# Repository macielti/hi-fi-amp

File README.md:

# Hi-Fi Audio Amplifier project

Class A audio amplifier project based on JLH 1969 project.

Lista de componentes com valores aproximados: [Lista de Componentes Eletrônicos](https://github.com/macielti/hi-fi-amp/blob/main/docs/Lista%20de%20Componentes%20Eletrônicos.md)

## Exemplo da placa Fonte de Alimentação montada

## Exemplo da placa Amplificadora de Áudio montada

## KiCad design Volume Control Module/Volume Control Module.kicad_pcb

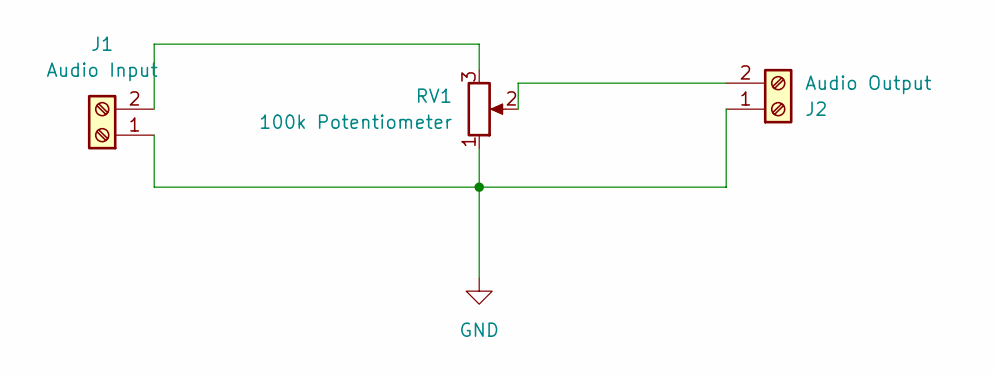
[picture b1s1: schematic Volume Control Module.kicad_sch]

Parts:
J1: Audio Input; TerminalBlock_MaiXu_MX126-5.0-02P_1x02_P5.00mm
J2: Audio Output; TerminalBlock_MaiXu_MX126-5.0-02P_1x02_P5.00mm
RV1: 100k Potentiometer; Potentiometer_Alps_RK163_Single_Horizontal

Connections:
GND: J1.1, J2.1, RV1.1
unnamed: J1.2, RV1.3
unnamed: J2.2, RV1.2

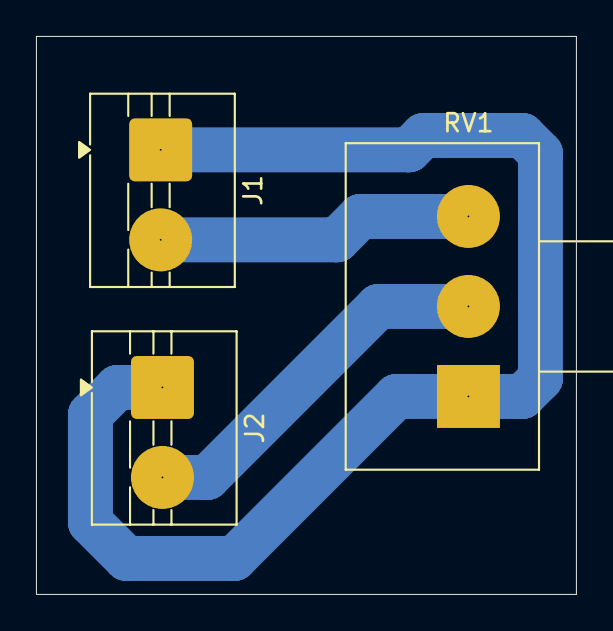
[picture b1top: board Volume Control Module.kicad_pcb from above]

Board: 2 copper layers, 30.0 x 31.0 mm, 3 parts (0 on the bottom side), 3 nets.

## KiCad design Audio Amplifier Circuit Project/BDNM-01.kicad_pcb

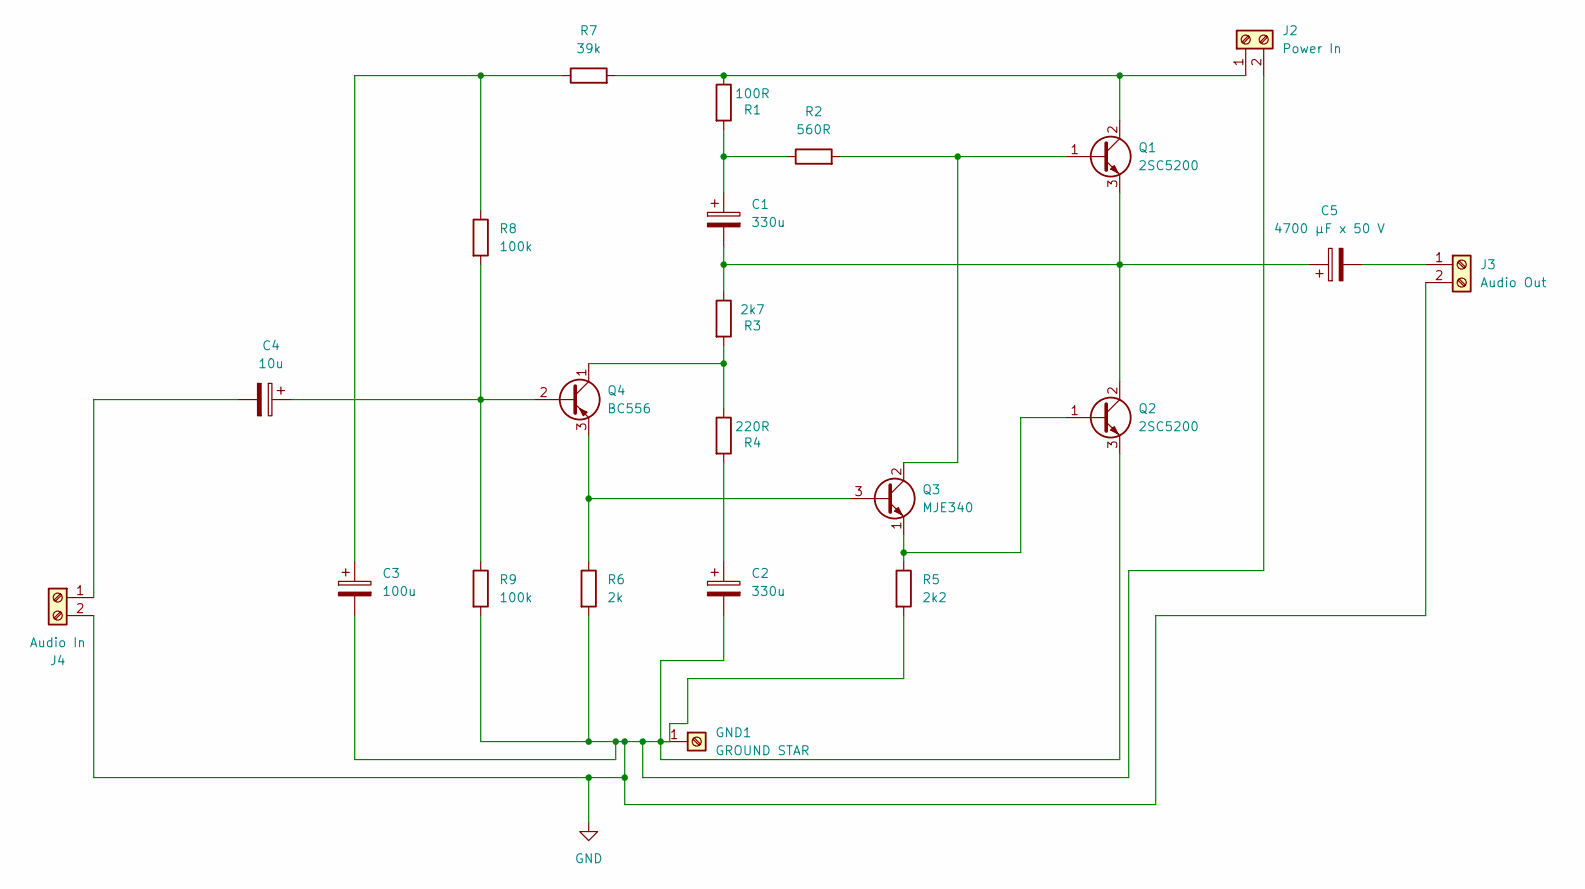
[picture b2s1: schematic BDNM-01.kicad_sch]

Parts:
C1, C2: 330u; CP_Radial_D10.0mm_P5.00mm
C3: 100u; CP_Radial_D6.3mm_P2.50mm
C4: 10u; CP_Radial_D5.0mm_P2.00mm
C5: 4700 µF x 50 V; CP_Radial_D22.0mm_P10.00mm_SnapIn
GND1: GROUND STAR; TestPoint_THTPad_D4.0mm_Drill2.0mm
J2: Power In; Altech_AK300_1x02_P5.00mm_45-Degree
J3: Audio Out; Altech_AK300_1x02_P5.00mm_45-Degree
J4: Audio In; Altech_AK300_1x02_P5.00mm_45-Degree
Q1, Q2: 2SC5200; TO-264-3_Vertical
Q3: MJE340; TO-220-3_Vertical
Q4: BC556; TO-92_Inline
R1: 100R; R_Axial_DIN0207_L6.3mm_D2.5mm_P10.16mm_Horizontal
R2: 560R; R_Axial_DIN0207_L6.3mm_D2.5mm_P10.16mm_Horizontal
R3: 2k7; R_Axial_DIN0207_L6.3mm_D2.5mm_P10.16mm_Horizontal
R4: 220R; R_Axial_DIN0207_L6.3mm_D2.5mm_P10.16mm_Horizontal
R5: 2k2; R_Axial_DIN0207_L6.3mm_D2.5mm_P10.16mm_Horizontal
R6: 2k; R_Axial_DIN0207_L6.3mm_D2.5mm_P10.16mm_Horizontal
R7: 39k; R_Axial_DIN0207_L6.3mm_D2.5mm_P10.16mm_Horizontal
R8, R9: 100k; R_Axial_DIN0207_L6.3mm_D2.5mm_P10.16mm_Horizontal

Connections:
GND: C2.2, C3.2, GND1.1, J2.2, J3.2, J4.2, Q2.3 (E), R5.2, R6.2, R9.2
unnamed: C1.1, R1.2, R2.1
unnamed: C2.1, R4.2
unnamed: C3.1, R7.1, R8.1
unnamed: J2.1, Q1.2 (C), R1.1, R7.2
unnamed: C5.2, J3.1
unnamed: C4.2, J4.1
unnamed: Q1.1 (B), Q3.2 (C), R2.2
unnamed: C1.2, C5.1, Q1.3 (E), Q2.2 (C), R3.1
unnamed: Q2.1 (B), Q3.1 (E), R5.1
unnamed: Q3.3 (B), Q4.3 (E), R6.1
unnamed: C4.1, Q4.2 (B), R8.2, R9.1
unnamed: Q4.1 (C), R3.2, R4.1

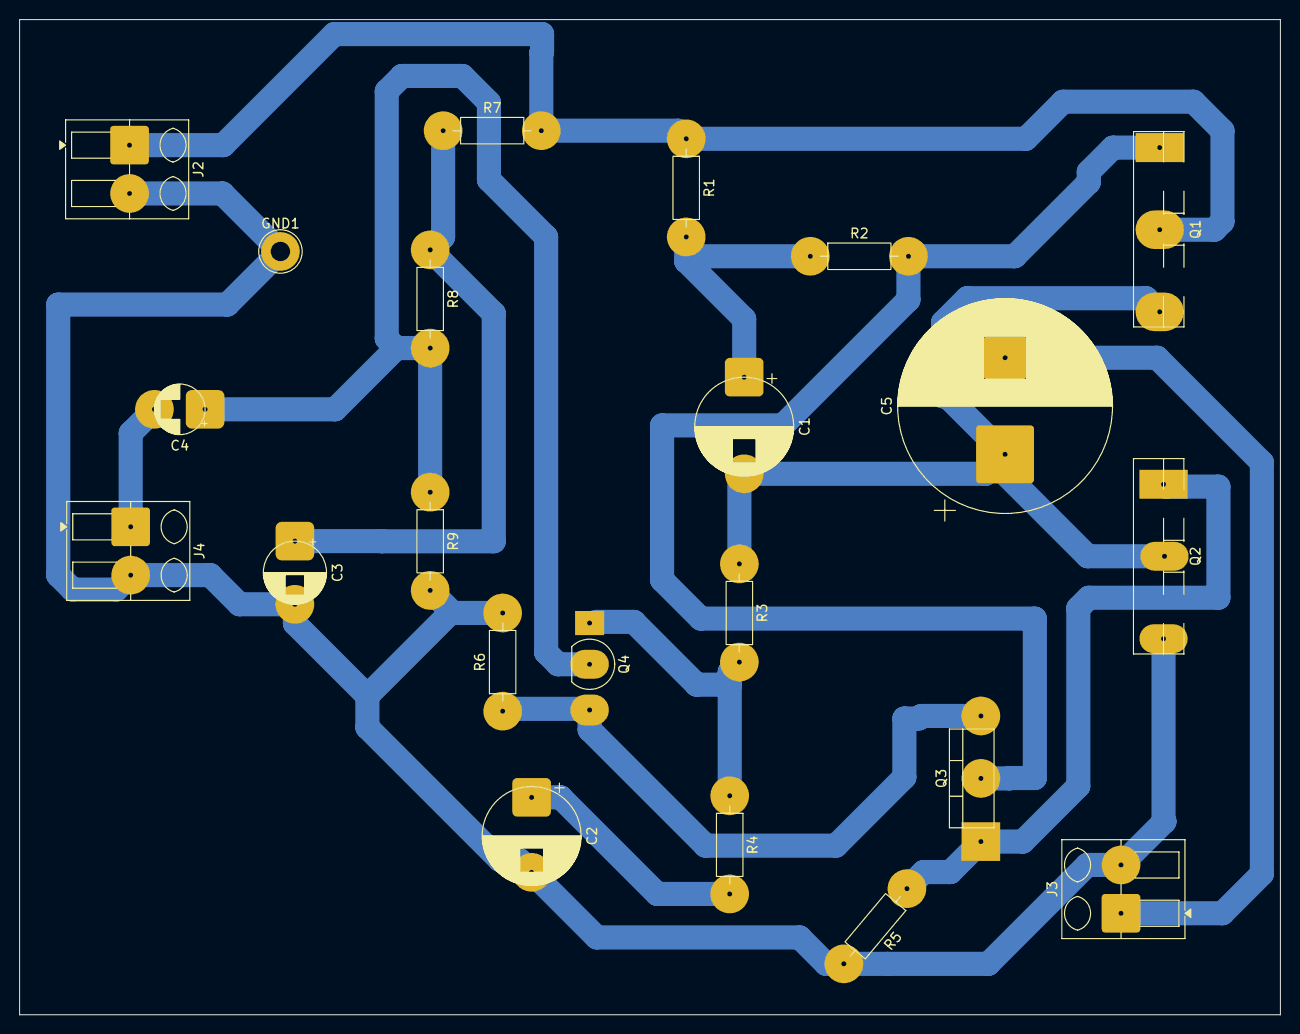
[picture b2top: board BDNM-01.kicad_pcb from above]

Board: 2 copper layers, 130.5 x 103.0 mm, 22 parts (0 on the bottom side), 13 nets.

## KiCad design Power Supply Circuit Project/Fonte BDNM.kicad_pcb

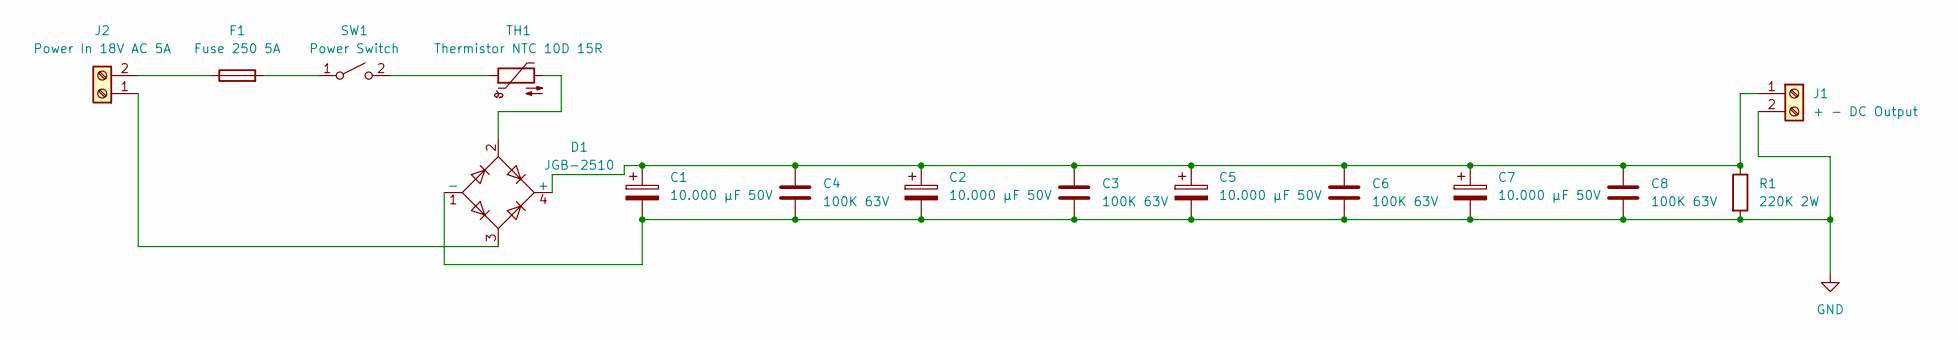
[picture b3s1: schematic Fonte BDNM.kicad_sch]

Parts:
C1, C2, C5, C7: 10.000 µF 50V; CP_Radial_D25.0mm_P10.00mm_SnapIn
C3, C4, C6, C8: 100K 63V; C_Rect_L7.2mm_W3.5mm_P5.00mm_FKS2_FKP2_MKS2_MKP2
D1: JGB-2510; Diode_Bridge_32.0x5.6x17.0mm_P10.0mm_P7.5mm
F1: Fuse 250 5A; Fuseholder_Cylinder-6.3x32mm_Schurter_0031-8002_Horizontal_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
J1: + - DC Output; TerminalBlock_MaiXu_MX126-5.0-02P_1x02_P5.00mm
J2: Power In 18V AC 5A; TerminalBlock_MaiXu_MX126-5.0-02P_1x02_P5.00mm
R1: 220K 2W; R_Axial_DIN0207_L6.3mm_D2.5mm_P7.62mm_Horizontal
SW1: Power Switch; TerminalBlock_MaiXu_MX126-5.0-02P_1x02_P5.00mm
TH1: Thermistor NTC 10D 15R; RV_Disc_D21.5mm_W6.1mm_P7.5mm

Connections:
GND: C1.2, C2.2, C3.2, C4.2, C5.2, C6.2, C7.2, C8.2, D1.1 (-), J1.2, R1.2
unnamed: C1.1, C2.1, C3.1, C4.1, C5.1, C6.1, C7.1, C8.1, D1.4 (+), J1.1, R1.1
unnamed: D1.2, TH1.2
unnamed: D1.3, J2.1
unnamed: F1.1, J2.2
unnamed: F1.2, SW1.1 (A)
unnamed: SW1.2 (B), TH1.1

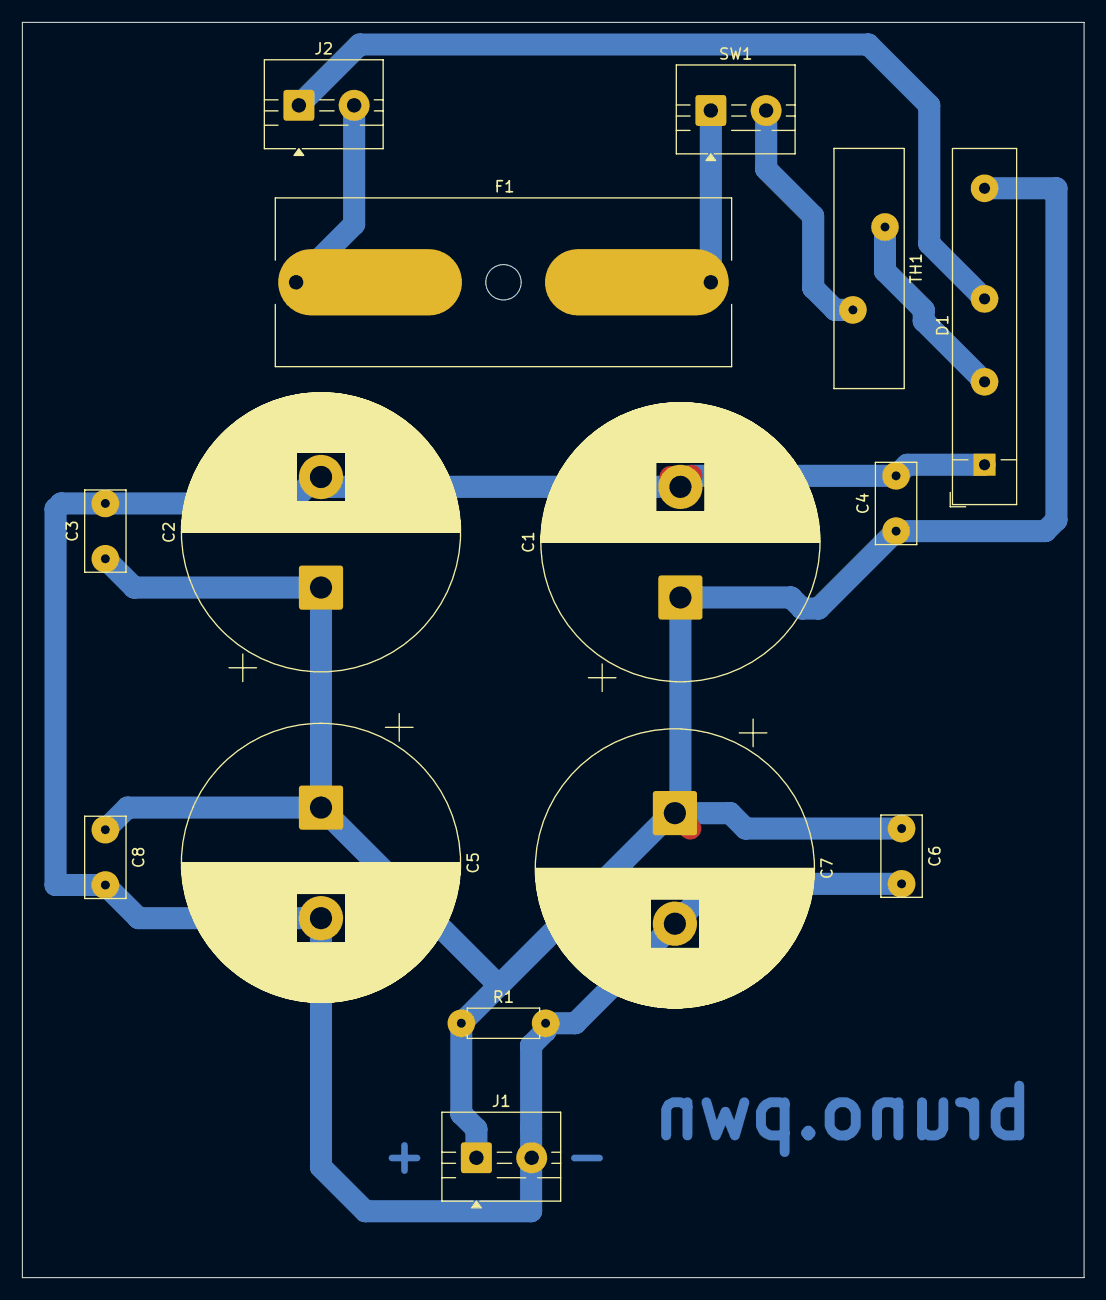
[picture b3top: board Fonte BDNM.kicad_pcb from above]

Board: 2 copper layers, 96.0 x 113.5 mm, 15 parts (0 on the bottom side), 7 nets.

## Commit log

2025-11-17 update readme file
2025-11-17 git ignore gile
2025-11-20 document cost of production
2025-11-20 fix document
2025-11-20 fix typo
2025-11-20 add images
2025-11-20 update image
2025-11-20 add files for milling
2025-11-20 milling deeper
2025-11-26 gcode for audio amp board
2025-11-26 more deep driling
2025-11-30 add volume control module
2025-11-30 drill more deep
